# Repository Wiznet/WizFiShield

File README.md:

# WizFi Shield
WizFi Shield utilizes fully certified [WizFi210](http://www.wiznet.co.kr/WizFi210) wifi module to provide your Arduino with wireless capability. 
SPI interface is used to allow for faster transmission speed and to free up the Arduino's UART.
All the software and hardware materials are freely available and open source.
 
# Features
- Ultra Low Power (34μA at the Standby mode)
- Operates with standard 802.11b/g/n access point at speed up to11Mbps (802.11b)
- Security Protocol: WEP, WPA/WPA2-PSK, Enterprise, EAP-FAST, EAP-TLS, EAP-TTLS, PEAP

## Hardware
These are PCB files for the WizFi Shield for Arduino. The files were created in the free & low cost EagleCad software available from [CadSoft](http://www.cadsoftusa.com/download-eagle/?language=en).

## Software
These are library source code of WizFi shield and example code.

Example codes are as below.

- Basic test
- Basic Server test
- Limited AP test
- UDP client test
- UDP server test
- Web client test
- Web server test
- Remote Car control example : [link](http://blog.wiznet.co.kr/controlling-rc-car-with-wizfi-shield/)

TimerOne : Timer 1 ISR library

## Documents
Manual for WizFi shield (Korean & English version)

## Revision History
Update Release : 2 August 2013

- Fix bug: SPI & PWM control pin conflict

Update Release : 28 May 2013

- Html parse lib added
- New examples added: RC car control using UDP & Web
- Some minor change on examples.

First release : Dec. 2012

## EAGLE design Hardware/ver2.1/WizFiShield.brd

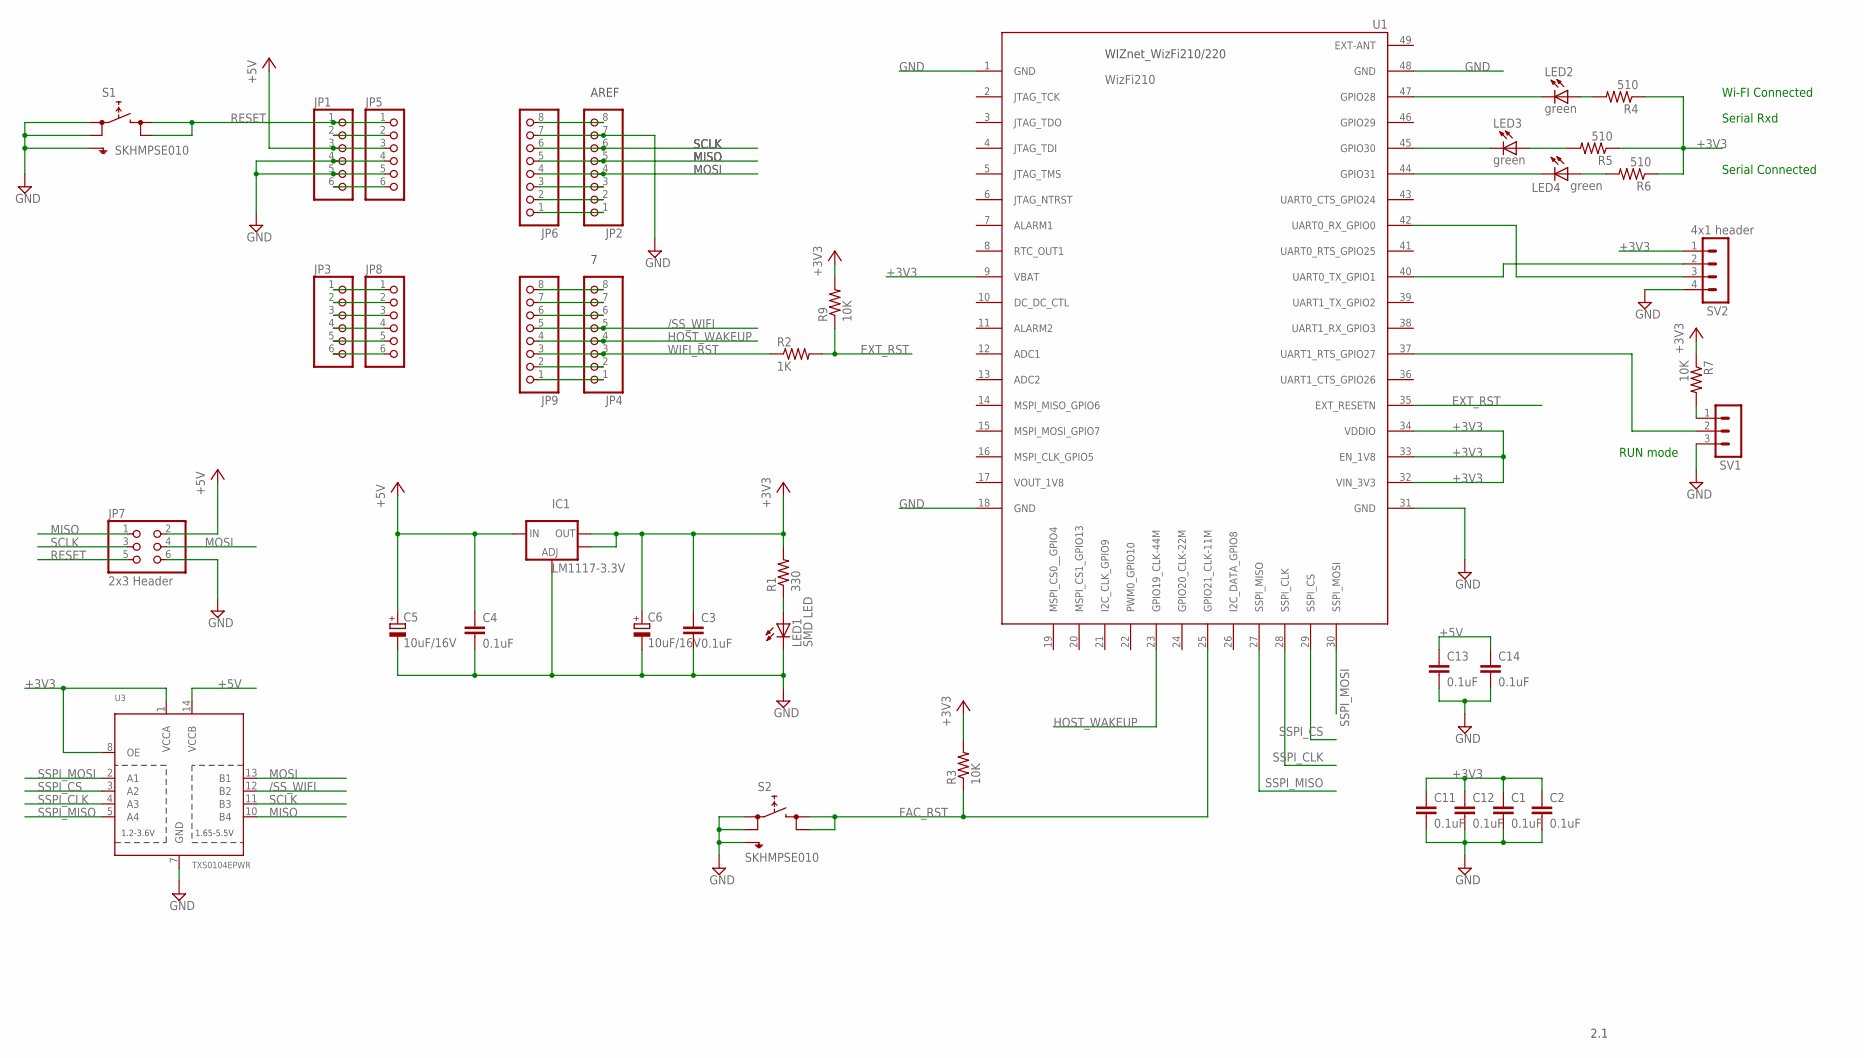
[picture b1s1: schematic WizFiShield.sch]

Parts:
C1, C2, C3, C4, C11, C12, C13, C14: 0.1uF; C0603
C5, C6: 10uF/16V; CT3216
IC1: LM1117-3.3V; SOT223
JP1, JP3, JP5, JP8: PINHD-1X6; 1X06
JP2, JP4, JP6, JP9: PINHD-1X8; 1X08
JP7: 2x3 Header; 2X03
LED1: SMD LED; CHIP-LED0805
LED2, LED3, LED4: green; CHIP-LED0805
R1: 330; R0805
R2: 1K; 0603-RES
R3, R7, R9: 10K; 0603-RES
R4, R5, R6: 510; 0603-RES
S1, S2: SKHMPSE010; SKHMPXE010
SV1: MA03-1
SV2: 4x1 header; MA04-1
U1: WizFi210; WIZFI210/220
U3: TXS0104EPWR; TSSOP14

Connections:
+3V3: C1.1, C2.1, C3.1, C6.+, C11.1, C12.1, IC1.2 (OUT), IC1.4 (OUT), R1.2, R3.2, R4.1, R5.1, R6.1, R7.1, R9.2, SV2.1, U1.9 (VBAT), U1.32 (VIN_3V3), U1.33 (EN_1V8), U1.34 (VDDIO), U3.1 (VCCA), U3.8 (OE)
+5V: C4.1, C5.+, C13.1, C14.1, IC1.3 (IN), JP1.3, JP5.3, JP7.2, U3.14 (VCCB)
/INT_WIZ: JP2.1, JP6.1
/RESET_WIZ: JP4.6, JP9.6
/SD_DET: JP4.8, JP9.8
/SS_SD: JP2.2, JP6.2
/SS_WIFI: JP4.5, JP9.5, U3.12 (B2)
/SS_WIZ: JP2.3, JP6.3
EXT_RST: R2.2, R9.1, U1.35 (EXT_RESETN)
FAC_RST: R3.1, S2.3 (2.1), S2.4 (2.2), U1.25 (GPIO21_CLK-11M)
GND: C1.2, C2.2, C3.2, C4.2, C5.-, C6.-, C11.2, C12.2, C13.2, C14.2, IC1.1 (ADJ), JP1.4, JP1.5, JP2.7, JP5.4, JP5.5, JP6.7, JP7.6, LED1.C, S1.1 (1.1), S1.2 (1.2), S1.5 (SH), S2.1 (1.1), S2.2 (1.2), S2.5 (SH), SV1.3, SV2.4, U1.1 (GND), U1.18 (GND), U1.31 (GND), U1.48 (GND), U3.7 (GND)
GPIO28: LED2.C, U1.47 (GPIO28)
GPIO30: LED3.C, U1.45 (GPIO30)
GPIO31: LED4.C, U1.44 (GPIO31)
HOST_WAKEUP: JP4.4, JP9.4, U1.23 (GPIO19_CLK-44M)
MISO: JP2.5, JP6.5, JP7.1, U3.10 (B4)
MOSI: JP2.4, JP6.4, JP7.4, U3.13 (B1)
unnamed: R7.2, SV1.1
unnamed: JP3.1, JP8.1
unnamed: JP3.2, JP8.2
unnamed: JP3.3, JP8.3
unnamed: SV1.2, U1.37 (UART1_RTS_GPIO27)
unnamed: JP3.4, JP8.4
unnamed: JP3.5, JP8.5
unnamed: JP3.6, JP8.6
unnamed: JP2.8, JP6.8
unnamed: JP4.2, JP9.2
unnamed: JP4.1, JP9.1
unnamed: JP1.6, JP5.6
unnamed: JP1.2, JP5.2
unnamed: LED1.A, R1.1
unnamed: LED2.A, R4.2
unnamed: LED3.A, R5.2
unnamed: LED4.A, R6.2
PWDN: JP4.7, JP9.7
RESET: JP1.1, JP5.1, JP7.5, S1.3 (2.1), S1.4 (2.2)
SCLK: JP2.6, JP6.6, JP7.3, U3.11 (B3)
SSPI_CLK: U1.28 (SSPI_CLK), U3.4 (A3)
SSPI_CS: U1.29 (SSPI_CS), U3.3 (A2)
SSPI_MISO: U1.27 (SSPI_MISO), U3.5 (A4)
SSPI_MOSI: U1.30 (SSPI_MOSI), U3.2 (A1)
UART0_RX: SV2.3, U1.42 (UART0_RX_GPIO0)
UART0_TX: SV2.2, U1.40 (UART0_TX_GPIO1)
WIFI_RST: JP4.3, JP9.3, R2.1

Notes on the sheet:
AREF
SCLK
MISO
MOSI
Wi-FI Connected
Serial Rxd
Serial Connected
RUN mode
2.1

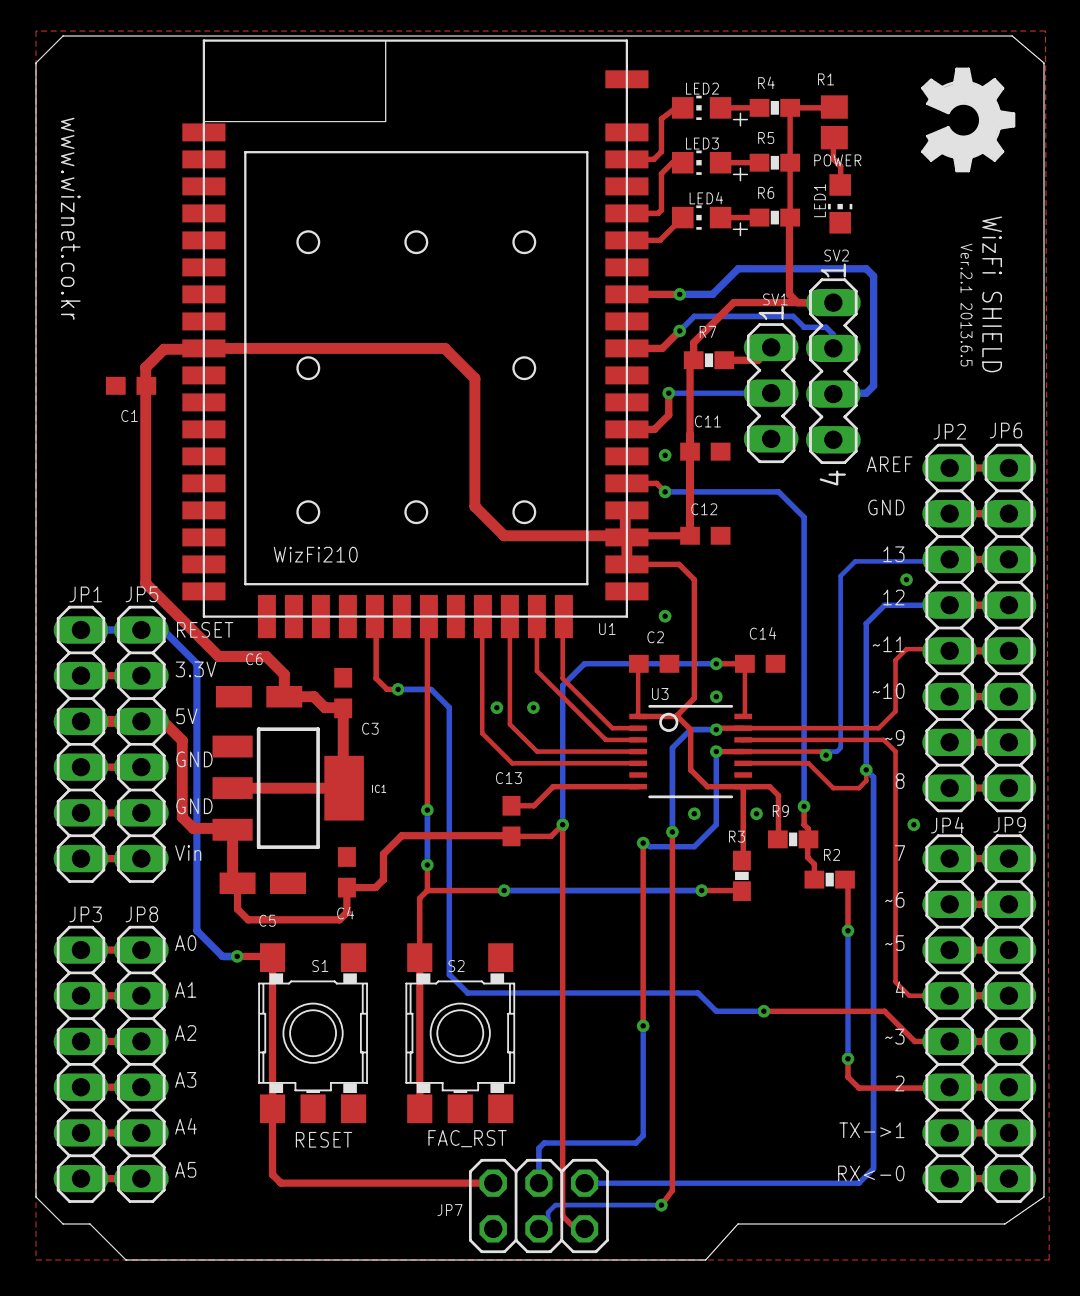
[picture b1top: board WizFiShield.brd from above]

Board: 2 copper layers, 56.0 x 68.0 mm, 39 parts (0 on the bottom side), 44 nets.

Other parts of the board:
U$1: OSHW_FILLX200_NOTEXT

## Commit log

2013-01-18 update read.me & hardware file
2013-01-18 Change title
2013-01-18 software & doc.
2013-01-18 change directory name
2013-01-18 update doc.
2013-01-18 update image
2013-01-18 change capital.
2013-04-22 Add English version Users manual
2013-04-23 Add English version document
2013-05-28 Update Lib & Examples
2013-08-02 Fix bug of WizFi_RC example
2014-01-14 Updated HTMLPages.cpp & HTMLPages.h
2014-02-27 pdf format schematic upload
2014-05-26 Upload ver.2.1 h/w
2016-07-26 fix compile error <PROGMEM>

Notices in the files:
parts and their libraries:
SparkFun: Licensing: CC v3.0 Share-Alike You are welcome to use this library for commercial purposes.
